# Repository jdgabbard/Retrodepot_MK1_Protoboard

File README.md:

# Retrodepot_MK1_Protoboard
RetroDepot MK1 Protoboard

This is one of the first protoboards that I designed.  I've included it here because it is still useful for small projects, and has a few options for connections.  This board technically predates the RetroDepot website.  However, it was used in some of the earlier projects that were shown on the site, such as the clone of Grant Searle's Z80 that I built.

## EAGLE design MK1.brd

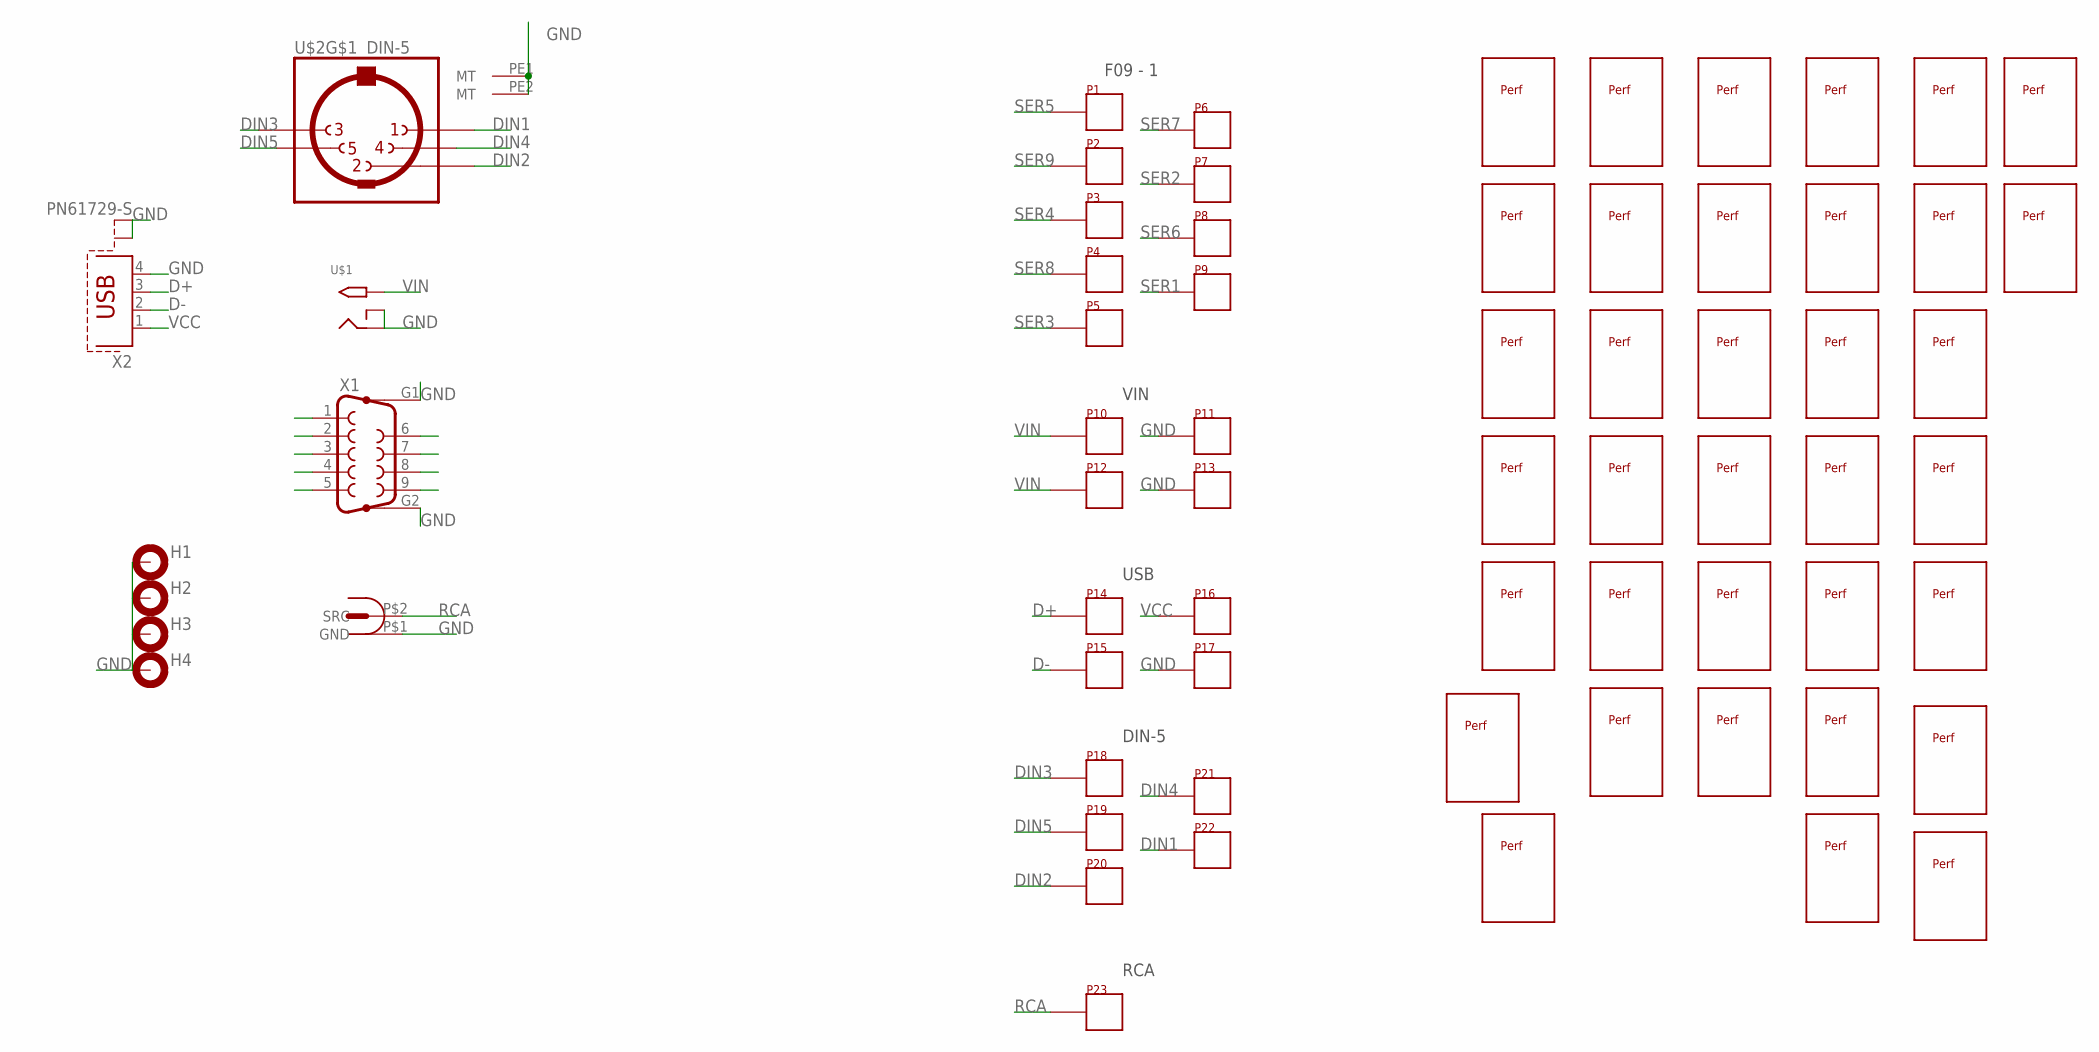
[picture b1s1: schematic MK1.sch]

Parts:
H1, H2, H3, H4: MOUNT-PAD-ROUND3.0; 3,0-PAD
P1, P2, P3, P4, P5, P6, P7, P8, P9, P10, P11, P12, P13, P14, P15, P16, P17, P18, P19, P20, P21, P22, P23: X3-PAD
U$1: 2.1MMJACKTHM; PJ-102A
U$2: DIN-5; CP-2350
U$3, U$4, U$5, U$6, U$7, U$8, U$9, U$10, U$11, U$12, U$13, U$14, U$15, U$16, U$17, U$18, U$19, U$20, U$21, U$22, U$23, U$24, U$25, U$26, U$27, U$28, U$29, U$30, U$31, U$32, U$33, U$34, U$35, U$36, U$37: PERF
U$38: RCA_VIDEO
X1: F09HP
X2: PN61729-S

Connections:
D+: P14.1, P14.2, P14.3, X2.3
D-: P15.1, P15.2, P15.3, X2.2
DIN1: P22.1, P22.2, P22.3, U$2.1
DIN2: P20.1, P20.2, P20.3, U$2.2
DIN3: P18.1, P18.2, P18.3, U$2.3
DIN4: P21.1, P21.2, P21.3, U$2.4
DIN5: P19.1, P19.2, P19.3, U$2.5
GND: H1.B3,0, H2.B3,0, H3.B3,0, H4.B3,0, P11.1, P11.2, P11.3, P13.1, P13.2, P13.3, P17.1, P17.2, P17.3, U$1.RING, U$1.RING_SW, U$2.PE1 (MT), U$2.PE2 (MT), U$38.P$1 (GND), X1.G1, X1.G2, X2.4, X2.S1, X2.S2
RCA: P23.1, P23.2, P23.3, U$38.P$2 (SRC)
SER1: P9.1, P9.2, P9.3, X1.1
SER2: P7.1, P7.2, P7.3, X1.2
SER3: P5.1, P5.2, P5.3, X1.3
SER4: P3.1, P3.2, P3.3, X1.4
SER5: P1.1, P1.2, P1.3, X1.5
SER6: P8.1, P8.2, P8.3, X1.6
SER7: P6.1, P6.2, P6.3, X1.7
SER8: P4.1, P4.2, P4.3, X1.8
SER9: P2.1, P2.2, P2.3, X1.9
VCC: P16.1, P16.2, P16.3, X2.1
VIN: P10.1, P10.2, P10.3, P12.1, P12.2, P12.3, U$1.TIP

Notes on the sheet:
F09 - 1
VIN
USB
DIN-5
RCA

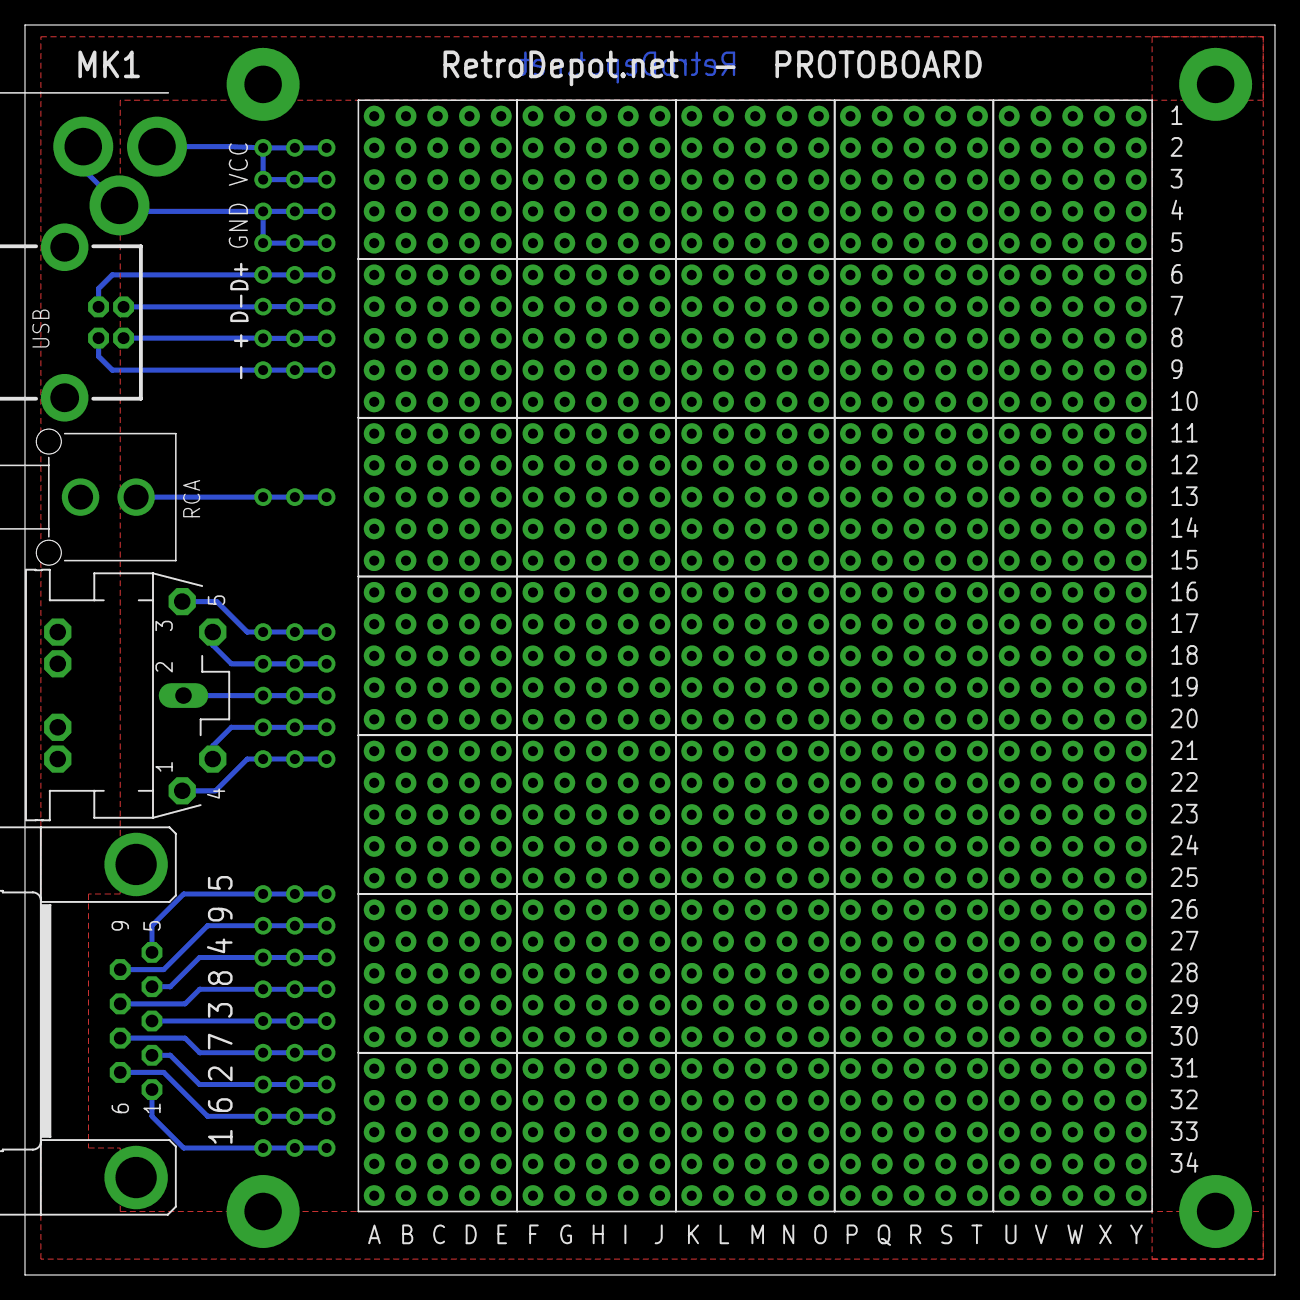
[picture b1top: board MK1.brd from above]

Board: 2 copper layers, 100.0 x 100.0 mm, 67 parts (0 on the bottom side), 20 nets.

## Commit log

2022-10-03 Initial Upload
2022-10-03 Picture Upload
2022-10-03 README Update
